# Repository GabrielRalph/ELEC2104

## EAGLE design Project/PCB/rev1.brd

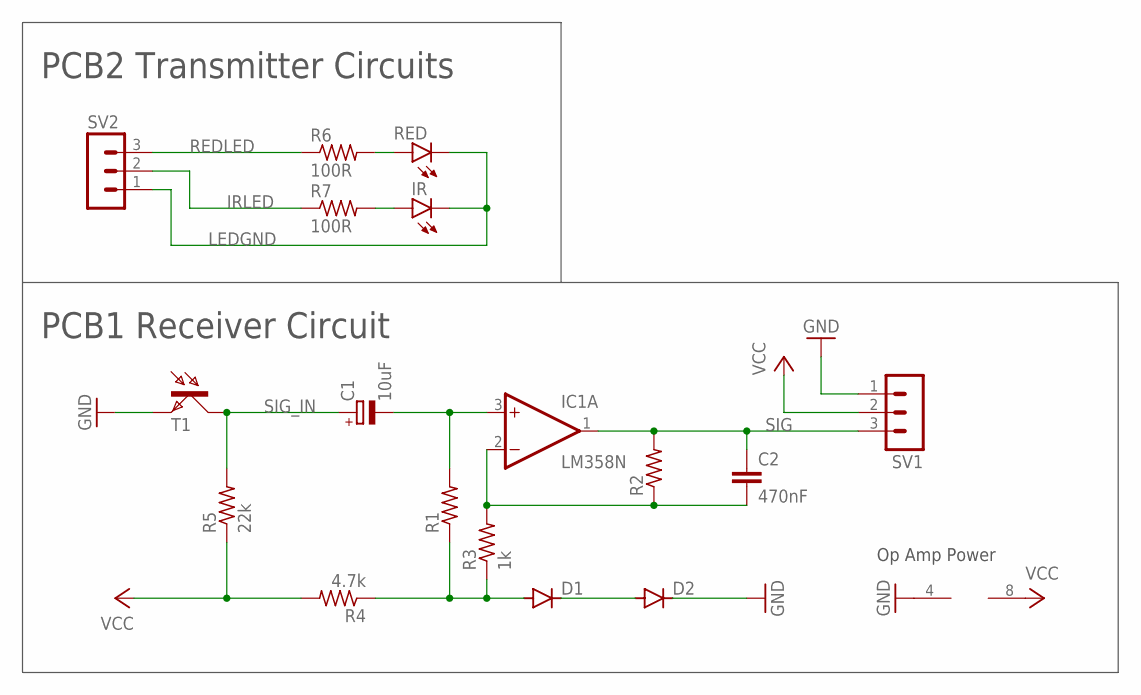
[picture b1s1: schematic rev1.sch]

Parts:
C1: 10uF; R/2012-12R
C2: 470nF; C2.5-3
D1, D2: 1N4148DO35-7; DO35-7
IC1: LM358N; DIL08
IR: LEDIRL80A; IRL80A
R1, R2: R-US_0207/7; 0207/7
R3: 1k; R0805
R4: 4.7k; 0207/7
R5: 22k; 0207/7
R6, R7: 100R; R0805
RED: LEDCHIPLED_0805; CHIPLED_0805
SV1, SV2: MA03-1
T1: LPT80A

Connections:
GND: D2.C, IC1.4 (V-), SV1.1, T1.E
IRLED: R7.1, SV2.2
LEDGND: IR.K (C), RED.C, SV2.1
unnamed: C1.-, IC1.3 (+IN), R1.2
unnamed: R6.2, RED.A
unnamed: C2.2, IC1.2 (-IN), R2.1, R3.2
unnamed: D1.C, D2.A
unnamed: IR.A, R7.2
unnamed: D1.A, R1.1, R3.1, R4.1
REDLED: R6.1, SV2.3
SIG: C2.1, IC1.1 (OUT), R2.2, SV1.3
SIG_IN: C1.+, R5.2, T1.C
VCC: IC1.8 (V+), R4.2, R5.1, SV1.2

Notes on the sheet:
PCB2 Transmitter Circuits
PCB1 Receiver Circuit
Op Amp Power

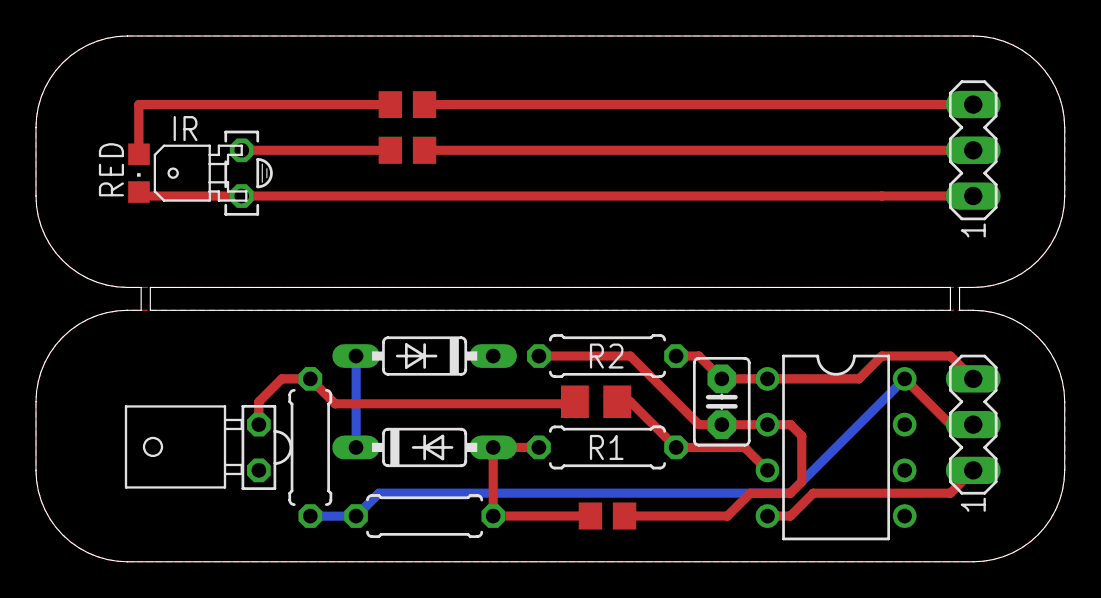
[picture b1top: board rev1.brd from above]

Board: 2 copper layers, 57.1 x 29.2 mm, 17 parts (0 on the bottom side), 13 nets.

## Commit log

2022-08-31 init
2022-08-31 more logs
2022-08-31 smaller range for osc logs
2022-08-31 Create CNAME
2022-08-31 Lab book photos
2022-08-31 test
2022-09-06 plot generator
2022-09-06 plot titles
2022-09-06 ignore stuff
2022-09-06 update figs
2022-09-06 everything
2022-09-06 plot updates
2022-09-06 wave dots
2022-09-07 lab 2 photos
2022-09-07 part4 photo
2022-09-13 fsheet
2022-09-14 circuit diagrams updates
2022-09-14 lab 3 data
2022-09-20 Add files via upload
    Lab3 lab book photos
2022-09-20 elvis logs now does 3wire + voltage transfer... idk and lab3 images
2022-09-20 plots updated
2022-09-20 find va using lin reg
2022-09-21 logs updated
2022-09-21 lab 4
2022-09-21 lab 4 folder
2022-09-25 equations
2022-09-25 kinda okay search
2022-09-25 up to lec 2 equations
2022-09-25 depletion
2022-09-25 edit
2022-09-25 fix eeek
2022-10-05 lab5
2022-10-05 edits
2022-10-12 major project
2022-10-12 commy
2022-10-12 Lab 5
2022-10-19 Oscilloscope readings for IR LED with square wave
    for figure 2
2022-10-26 Test prototype heartbeat data
2022-11-01 pcb design
2022-11-02 Rename PrototypeCircuitTesting.txt to PrototypeCircuitTestingIRLED.txt
2022-11-02 Rename heart_beat.txt to heart_beatIRLED.txt
2022-11-02 Rename PrototypeCircuitTestingIRLED.txt to Req1PrototypeCircuitTestingIRLED.txt
2022-11-02 Rename heart_beatIRLED.txt to Req1_heart_beatIRLED.txt
2022-11-02 Rename Req1PrototypeCircuitTestingIRLED.txt to Req1_PrototypeCircuitTestingIRLED.txt
2022-11-02 Photos from phone for evidence
2022-11-02 Files from 2/11
2022-11-03 added stl files for print
2022-11-08 clip spring
2022-11-08 clip
2022-11-08 Latest Version of STLs
2022-11-08 new testing photo
2022-11-08 replace bad led png
2022-11-09 updates more figures
2022-11-09 final updates
2022-11-09 more figs
2022-11-09 pictures
2022-11-09 photos
2022-11-09 more code
2022-11-09 all in project
2022-11-15 more updates to equations
2022-11-17 updates to equations
2022-11-17 crazey matlab paste
